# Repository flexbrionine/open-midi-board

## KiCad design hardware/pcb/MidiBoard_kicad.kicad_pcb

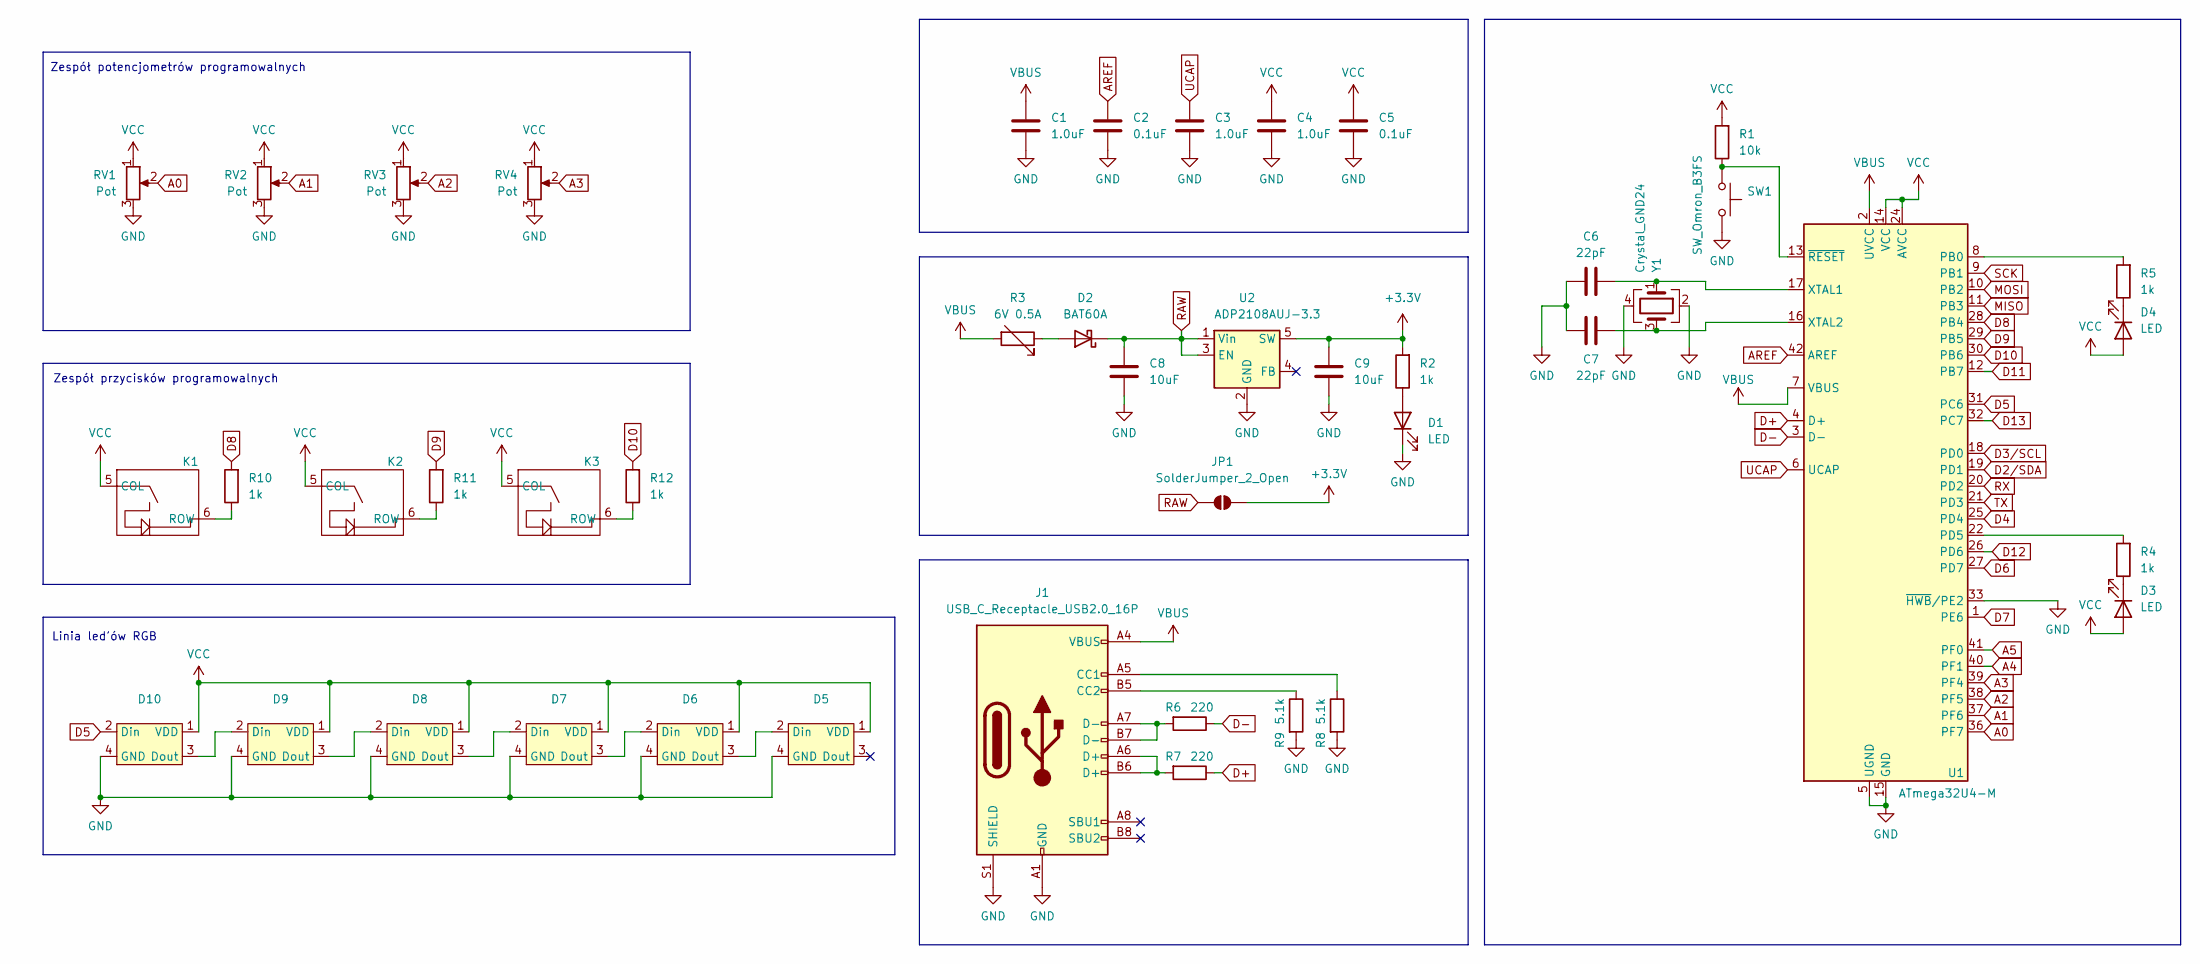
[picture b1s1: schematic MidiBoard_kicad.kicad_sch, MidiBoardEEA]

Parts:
C1, C3, C4: 1.0uF; C_0402_1005Metric
C2, C5: 0.1uF; C_0402_1005Metric
C6, C7: 22pF; C_0805_2012Metric
C8, C9: 10uF; C_0603_1608Metric
D1, D3, D4: LED; LED_0603_1608Metric
D2: BAT60A; D_SOD-323
D5, D6, D7, D8, D9, D10: WS3238
J1: USB_C_Receptacle_USB2.0_16P; USB_C_Receptacle_GCT_USB4105-xx-A_16P_TopMnt_Horizontal
JP1: SolderJumper_2_Open; SolderJumper-2_P1.3mm_Open_TrianglePad1.0x1.5mm
K1, K2, K3: MX_FHS_5pinRGB_FP
R1: 10k; R_0402_1005Metric
R2, R4, R5, R10, R11, R12: 1k; R_0402_1005Metric
R3: 6V 0.5A; R_0805_2012Metric
R6, R7: 220; R_0402_1005Metric
R8, R9: 5.1k; R_0402_1005Metric
RV1, RV2, RV3, RV4: Pot; Potentiometer_Piher_T-16L_Single_Vertical_Hole
SW1: SW_Omron_B3FS; SW_SPST_Omron_B3FS-100xP
U1: ATmega32U4-M; QFN-44-1EP_7x7mm_P0.5mm_EP5.15x5.15mm
U2: ADP2108AUJ-3.3; TSOT-23-5
Y1: Crystal_GND24; Crystal_SMD_0603-4Pin_6.0x3.5mm

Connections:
+3.3V: C9.1, JP1.2 (B), R2.2, U2.5 (SW)
A0: RV1.2, U1.36 (PF7)
A1: RV2.2, U1.37 (PF6)
A2: RV3.2, U1.38 (PF5)
A3: RV4.2, U1.39 (PF4)
A4: U1.40 (PF1)
A5: U1.41 (PF0)
AREF: C2.1, U1.42 (AREF)
D2/SDA: U1.19 (PD1)
D3/SCL: U1.18 (PD0)
D4: U1.25 (PD4)
D5: D10.2 (Din), U1.31 (PC6)
D6: U1.27 (PD7)
D7: U1.1 (PE6)
D8: R10.2, U1.28 (PB4)
D9: R11.2, U1.29 (PB5)
D10: R12.2, U1.30 (PB6)
D11: U1.12 (PB7)
D12: U1.26 (PD6)
D13: U1.32 (PC7)
D+: R7.1, U1.4 (D+)
D-: R6.1, U1.3 (D-)
GND: C1.2, C2.2, C3.2, C4.2, C5.2, C6.1, C7.1, C8.2, C9.2, D1.1 (K), D5.4 (GND), D6.4 (GND), D7.4 (GND), D8.4 (GND), D9.4 (GND), D10.4 (GND), J1.A1 (GND), J1.A12 (GND), J1.B1 (GND), J1.B12 (GND), J1.S1 (SHIELD), R8.2, R9.2, RV1.3, RV2.3, RV3.3, RV4.3, SW1.2, U1.5 (UGND), U1.15 (GND), U1.23 (GND), U1.33 (~HWB/PE2), U1.35 (GND), U1.43 (GND), U1.45 (GND), U2.2 (GND), Y1.2, Y1.4
MISO: U1.11 (PB3)
MOSI: U1.10 (PB2)
unnamed: D1.2 (A), R2.1
unnamed: D2.2 (A), R3.1
unnamed: D3.1 (K), R4.1
unnamed: D4.1 (K), R5.1
unnamed: D5.2 (Din), D6.3 (Dout)
unnamed: D6.2 (Din), D7.3 (Dout)
unnamed: D7.2 (Din), D8.3 (Dout)
unnamed: D8.2 (Din), D9.3 (Dout)
unnamed: D9.2 (Din), D10.3 (Dout)
unnamed: J1.A5 (CC1), R8.1
unnamed: J1.B5 (CC2), R9.1
unnamed: J1.A6 (D+), J1.B6 (D+), R7.2
unnamed: J1.A7 (D-), J1.B7 (D-), R6.2
unnamed: K1.6 (ROW), R10.1
unnamed: K2.6 (ROW), R11.1
unnamed: K3.6 (ROW), R12.1
unnamed: R5.2, U1.8 (PB0)
unnamed: R4.2, U1.22 (PD5)
unnamed: C6.2, U1.17 (XTAL1), Y1.1
unnamed: C7.2, U1.16 (XTAL2), Y1.3
unnamed: R1.1, SW1.1, U1.13 (~RESET)
RAW: C8.1, D2.1 (K), JP1.1 (A), U2.1 (Vin), U2.3 (EN)
RX: U1.20 (PD2)
SCK: U1.9 (PB1)
TX: U1.21 (PD3)
UCAP: C3.1, U1.6 (UCAP)
VBUS: C1.1, J1.A4 (VBUS), J1.A9 (VBUS), J1.B4 (VBUS), J1.B9 (VBUS), R3.2, U1.2 (UVCC), U1.7 (VBUS)
VCC: C4.1, C5.1, D3.2 (A), D4.2 (A), D5.1 (VDD), D6.1 (VDD), D7.1 (VDD), D8.1 (VDD), D9.1 (VDD), D10.1 (VDD), K1.5 (COL), K2.5 (COL), K3.5 (COL), R1.2, RV1.1, RV2.1, RV3.1, RV4.1, U1.14 (VCC), U1.24 (AVCC), U1.34 (VCC), U1.44 (AVCC)

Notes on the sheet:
Zespół potencjometrów programowalnych
Zespół przycisków programowalnych
Linia led'ów RGB

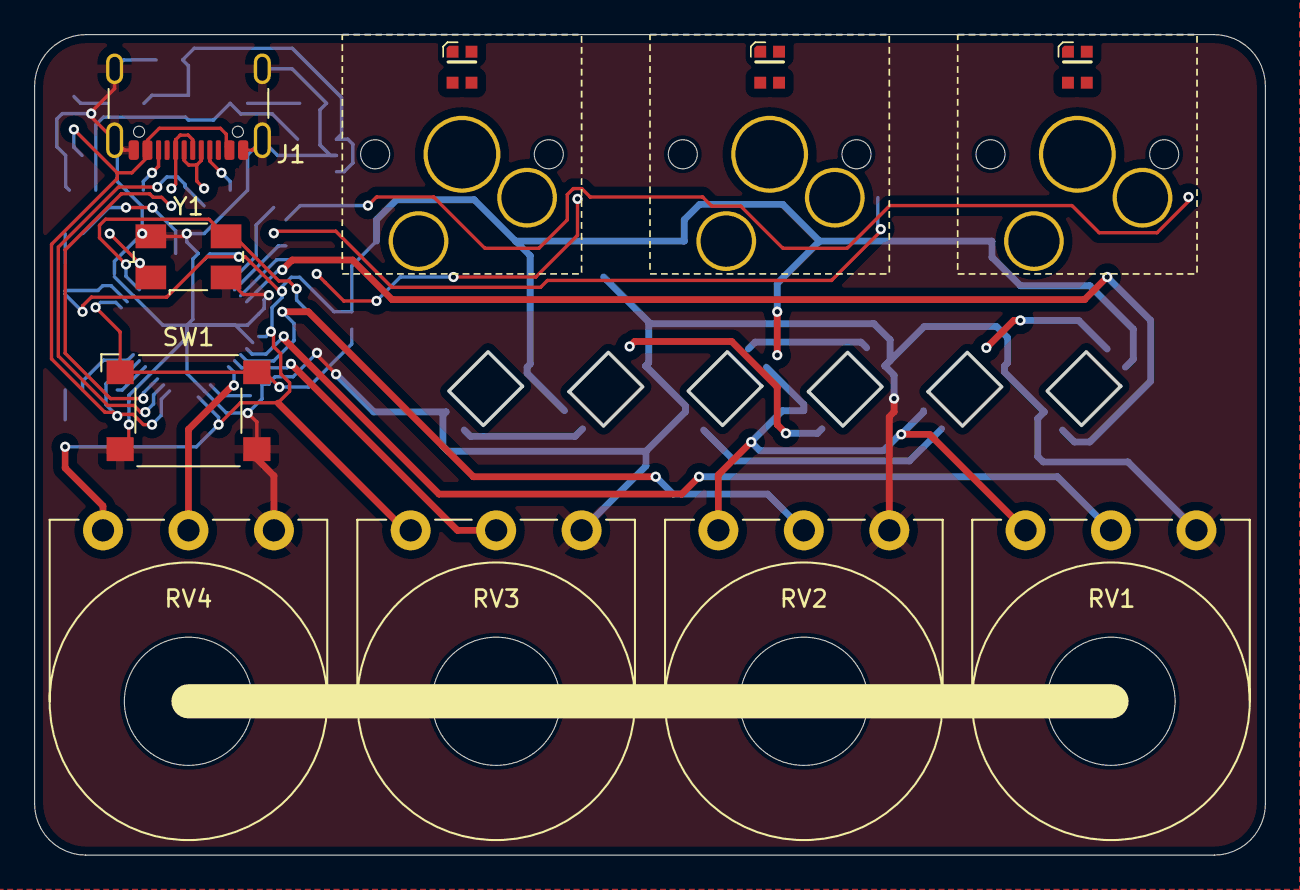
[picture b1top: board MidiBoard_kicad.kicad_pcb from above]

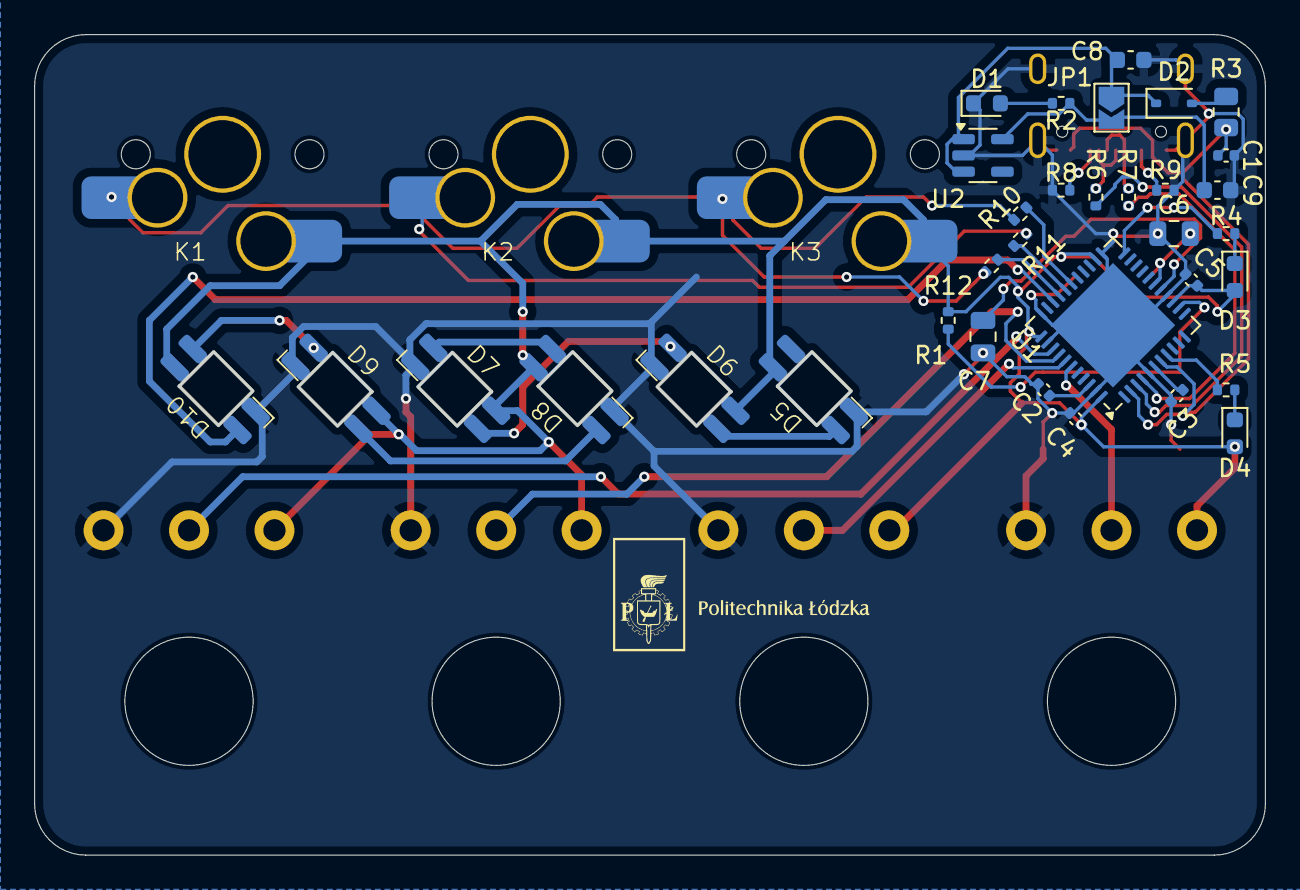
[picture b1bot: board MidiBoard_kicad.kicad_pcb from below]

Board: 2 copper layers, 71.9 x 47.9 mm, 44 parts (28 on the bottom side), 38 nets.

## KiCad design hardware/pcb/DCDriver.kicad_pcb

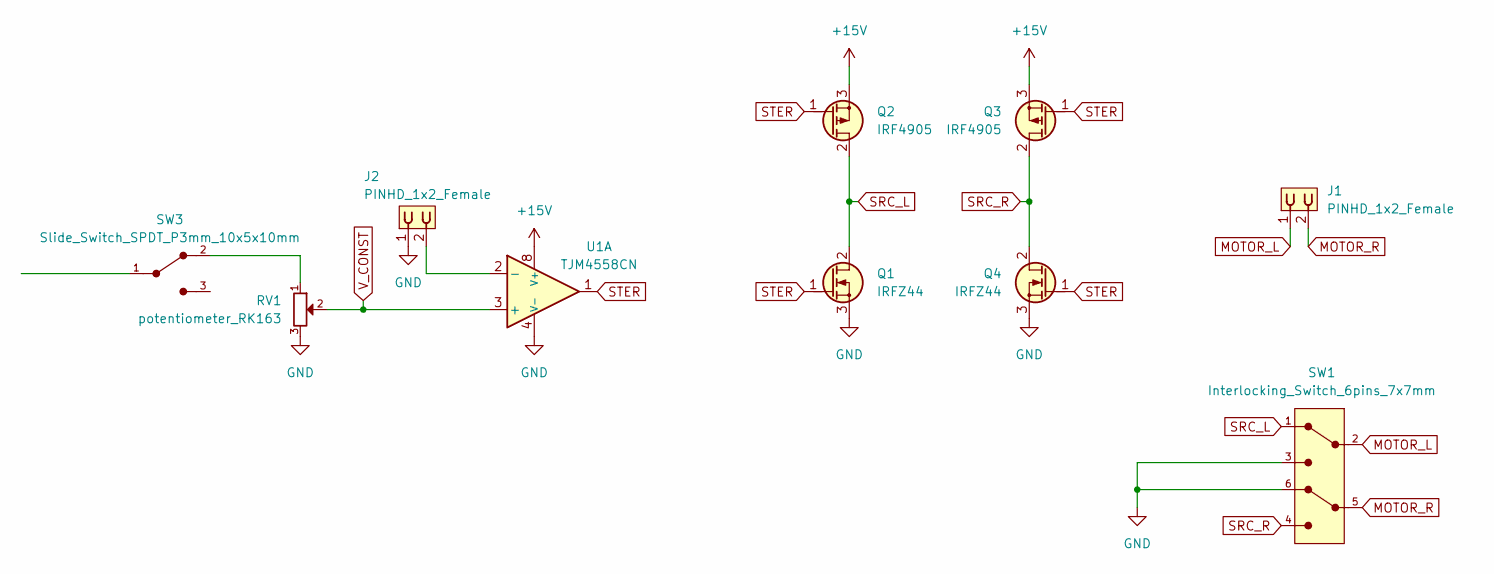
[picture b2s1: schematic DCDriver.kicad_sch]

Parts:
J1, J2: PINHD_1x2_Female; PinSocket_1x02_P2.54mm_Vertical
Q1, Q4: IRFZ44; TO-220-3_Vertical_GDS
Q2, Q3: IRF4905; TO-220-3_Vertical_GDS
RV1: potentiometer_RK163; Potentiometer_Alps_RK163_Single_Horizontal
SW1: Interlocking_Switch_6pins_7x7mm; Interlocking_Switch_6-pin_7x7mm
SW3: Slide_Switch_SPDT_P3mm_10x5x10mm
U1: TJM4558CN; DIP-8_W7.62mm_LongPads

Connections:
+15V: Q2.3 (S), Q3.3 (S), U1.8 (V+)
GND: J2.1, Q1.3 (S), Q4.3 (S), RV1.3, SW1.3, SW1.6, U1.4 (V-)
MOTOR_L: J1.1, SW1.2
MOTOR_R: J1.2, SW1.5
unnamed: RV1.1, SW3.2
unnamed: J2.2, U1.2 (-)
SRC_L: Q1.2 (D), Q2.2 (D), SW1.1
SRC_R: Q3.2 (D), Q4.2 (D), SW1.4
STER: Q1.1 (G), Q2.1 (G), Q3.1 (G), Q4.1 (G), U1.1
V_CONST: RV1.2, U1.3 (+)

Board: 2 copper layers, 10 parts (0 on the bottom side), 10 nets, no tracks yet.

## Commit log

2025-01-20 v1.0
    PCB (KiCad 8.0) project added
2025-01-20 v1.1
2025-01-24 v1.1.1
2026-02-15 Bump python-multipart
    Bumps [python-multipart](https://github.com/Kludex/python-multipart) from 0.0.19 to 0.0.22.
    - [Release notes](https://github.com/Kludex/python-multipart/releases)
    - [Changelog](https://github.com/Kludex/python-multipart/blob/master/CHANGELOG.md)
    - [Commits](https://github.com/Kludex/python-multipart/compare/0.0.19...0.0.22)
    ---
    updated-dependencies:
2026-05-12 Bump python-multipart
    Bumps [python-multipart](https://github.com/Kludex/python-multipart) from 0.0.22 to 0.0.27.
    - [Release notes](https://github.com/Kludex/python-multipart/releases)
    - [Changelog](https://github.com/Kludex/python-multipart/blob/main/CHANGELOG.md)
    - [Commits](https://github.com/Kludex/python-multipart/compare/0.0.22...0.0.27)
    ---
    updated-dependencies:
